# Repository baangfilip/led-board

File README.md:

# led-board learning project
Files relating to led-board.
Not anywhere near recommending to use any of this for something. 

Using IS31FL3731 as a led driver to control all the leds individually. 
Using Attiny85 to control IS31FL3731 via i2c. 

Powered by cr2032 battery.
 
Almost copied from https://github.com/adafruit/Adafruit_IS31FL3731

# v0.x1
Which actually was multiple different boards.

# v.02

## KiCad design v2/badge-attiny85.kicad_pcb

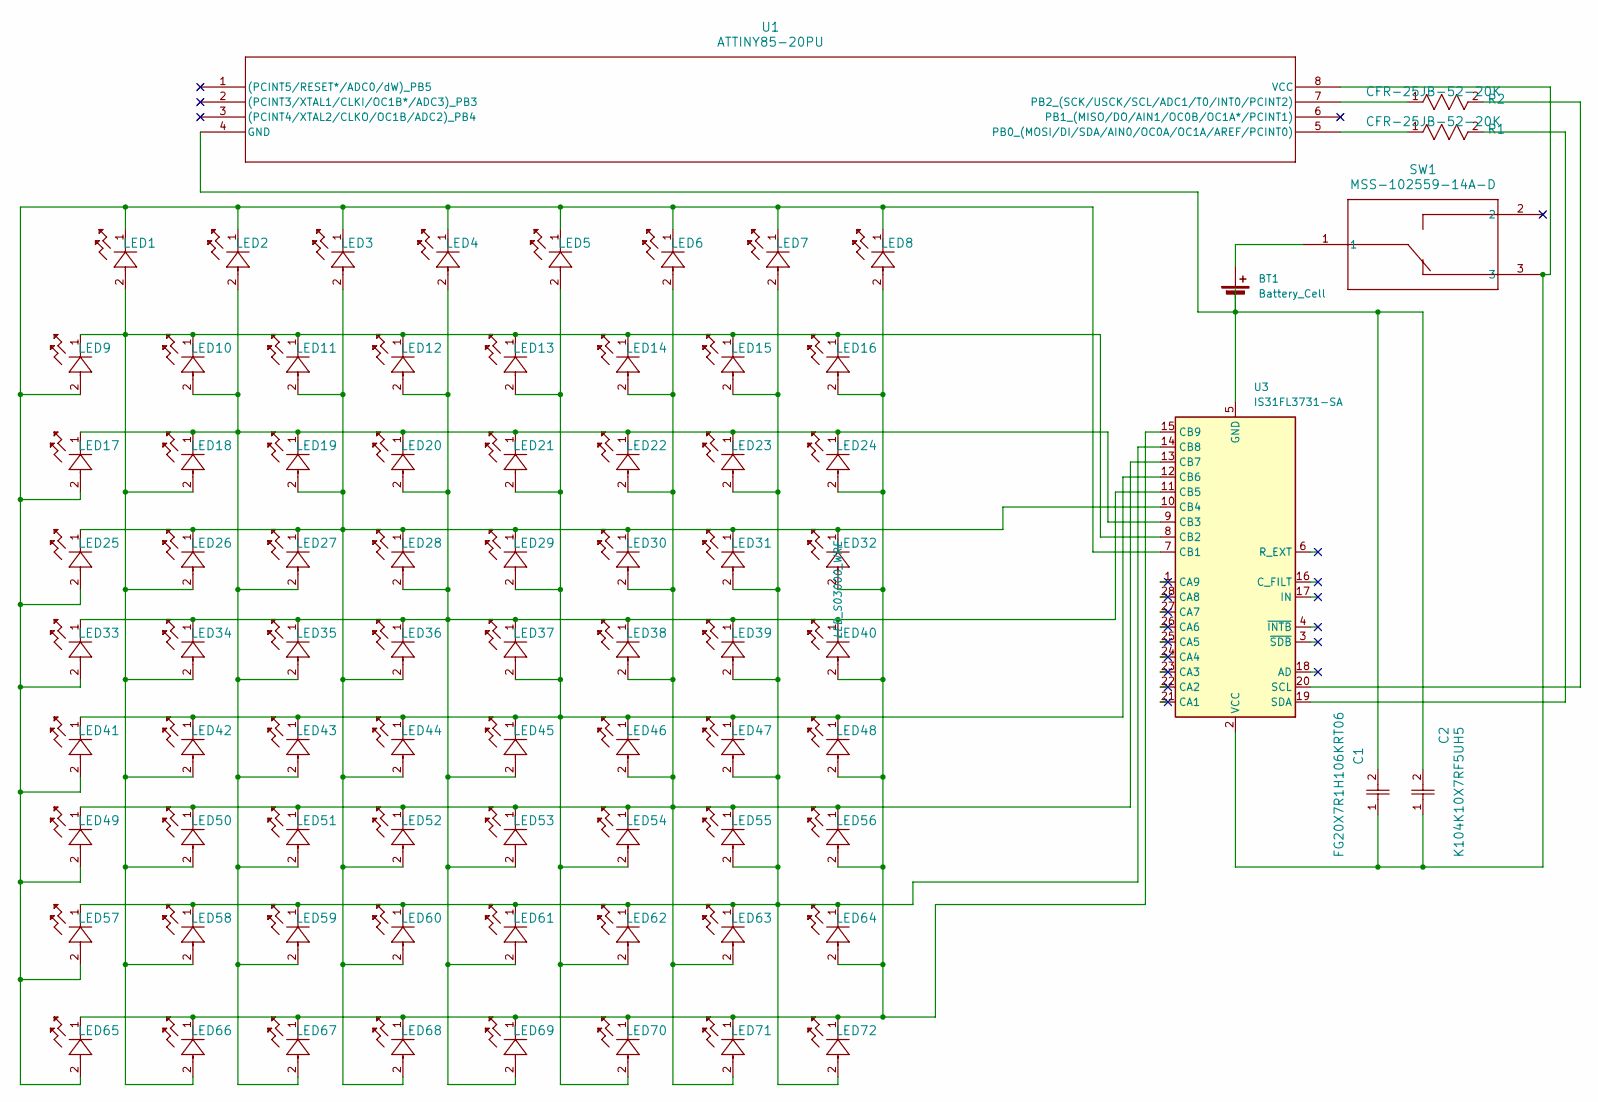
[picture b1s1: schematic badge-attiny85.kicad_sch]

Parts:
BT1: Battery_Cell; BatteryHolder_Multicomp_BC-2001_1x2032
C1: FG20X7R1H106KRT06; CAP_FG20_TDK
C2: K104K10X7RF5UH5; K104K10X7RF5UH5_VIS
LED1, LED2, LED3, LED4, LED5, LED6, LED7, LED8, LED9, LED10, LED11, LED12, LED13, LED14, LED15, LED16, LED17, LED18, LED19, LED20, LED21, LED22, LED23, LED24, LED25, LED26, LED27, LED28, LED29, LED30, LED31, LED32, LED33, LED34, LED35, LED36, LED37, LED38, LED39, LED40, LED41, LED42, LED43, LED44, LED45, LED46, LED47, LED48, LED49, LED50, LED51, LED52, LED53, LED54, LED55, LED56, LED57, LED58, LED59, LED60, LED61, LED62, LED63, LED64, LED65, LED66, LED67, LED68, LED69, LED70, LED71, LED72: LED_S03000_WRE
R1, R2: CFR-25JB-52-20K; YAG_CFR25_YAG
SW1: MSS-102559-14A-D; SW3_MSS-102559-14A-D_CUD
U1: ATTINY85-20PU; 8P3_ATM
U3: IS31FL3731-SA; SSOP-28_5.3x10.2mm_P0.65mm

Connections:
unnamed: BT1.1 (+), SW1.1
unnamed: BT1.2 (-), C1.2, C2.2, U1.4 (GND), U3.5 (GND)
unnamed: R1.1, U1.5 (PB0_(MOSI/DI/SDA/AIN0/OC0A/OC1A/AREF/PC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)
unnamed: R2.1, U1.7 (PB2_(SCK/USCK/SCL/ADC1/T0/INT0/PCINT2))
unnamed: C1.1, C2.1, SW1.3, U1.8 (VCC), U3.2 (VCC)
unnamed: LED1.1, LED2.1, LED3.1, LED4.1, LED5.1, LED6.1, LED7.1, LED8.1, LED9.2, LED17.2, LED25.2, LED33.2, LED41.2, LED49.2, LED57.2, LED65.2, U3.7 (CB1)
unnamed: LED1.2, LED9.1, LED10.1, LED11.1, LED12.1, LED13.1, LED14.1, LED15.1, LED16.1, LED18.2, LED26.2, LED34.2, LED42.2, LED50.2, LED58.2, LED66.2, U3.8 (CB2)
unnamed: LED2.2, LED10.2, LED17.1, LED18.1, LED19.1, LED20.1, LED21.1, LED22.1, LED23.1, LED24.1, LED27.2, LED35.2, LED43.2, LED51.2, LED59.2, LED67.2, U3.9 (CB3)
unnamed: LED3.2, LED11.2, LED19.2, LED25.1, LED26.1, LED27.1, LED28.1, LED29.1, LED30.1, LED31.1, LED32.1, LED36.2, LED44.2, LED52.2, LED60.2, LED68.2, U3.10 (CB4)
unnamed: LED4.2, LED12.2, LED20.2, LED28.2, LED33.1, LED34.1, LED35.1, LED36.1, LED37.1, LED38.1, LED39.1, LED40.1, LED45.2, LED53.2, LED61.2, LED69.2, U3.11 (CB5)
unnamed: LED5.2, LED13.2, LED21.2, LED29.2, LED37.2, LED41.1, LED42.1, LED43.1, LED44.1, LED45.1, LED46.1, LED47.1, LED48.1, LED54.2, LED62.2, LED70.2, U3.12 (CB6)
unnamed: LED6.2, LED14.2, LED22.2, LED30.2, LED38.2, LED46.2, LED49.1, LED50.1, LED51.1, LED52.1, LED53.1, LED54.1, LED55.1, LED56.1, LED63.2, LED71.2, U3.13 (CB7)
unnamed: LED7.2, LED15.2, LED23.2, LED31.2, LED39.2, LED47.2, LED55.2, LED57.1, LED58.1, LED59.1, LED60.1, LED61.1, LED62.1, LED63.1, LED64.1, LED72.2, U3.14 (CB8)
unnamed: LED8.2, LED16.2, LED24.2, LED32.2, LED40.2, LED48.2, LED56.2, LED64.2, LED65.1, LED66.1, LED67.1, LED68.1, LED69.1, LED70.1, LED71.1, LED72.1, U3.15 (CB9)
unnamed: R2.2, U3.20 (SCL)
unnamed: R1.2, U3.19 (SDA)

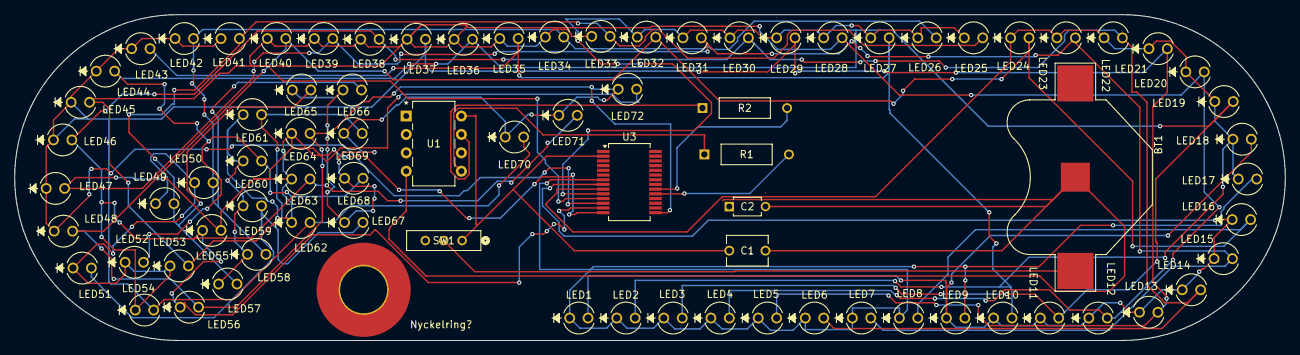
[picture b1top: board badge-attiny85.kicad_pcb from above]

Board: 2 copper layers, 175.5 x 45.0 mm, 81 parts (0 on the bottom side), 16 nets.

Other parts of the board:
Nyckelring?: MountingHole_6.5mm_Pad_TopBottom

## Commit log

2025-03-20 Intial commit of the old stuff
2025-03-20 Add where I got how-to from
